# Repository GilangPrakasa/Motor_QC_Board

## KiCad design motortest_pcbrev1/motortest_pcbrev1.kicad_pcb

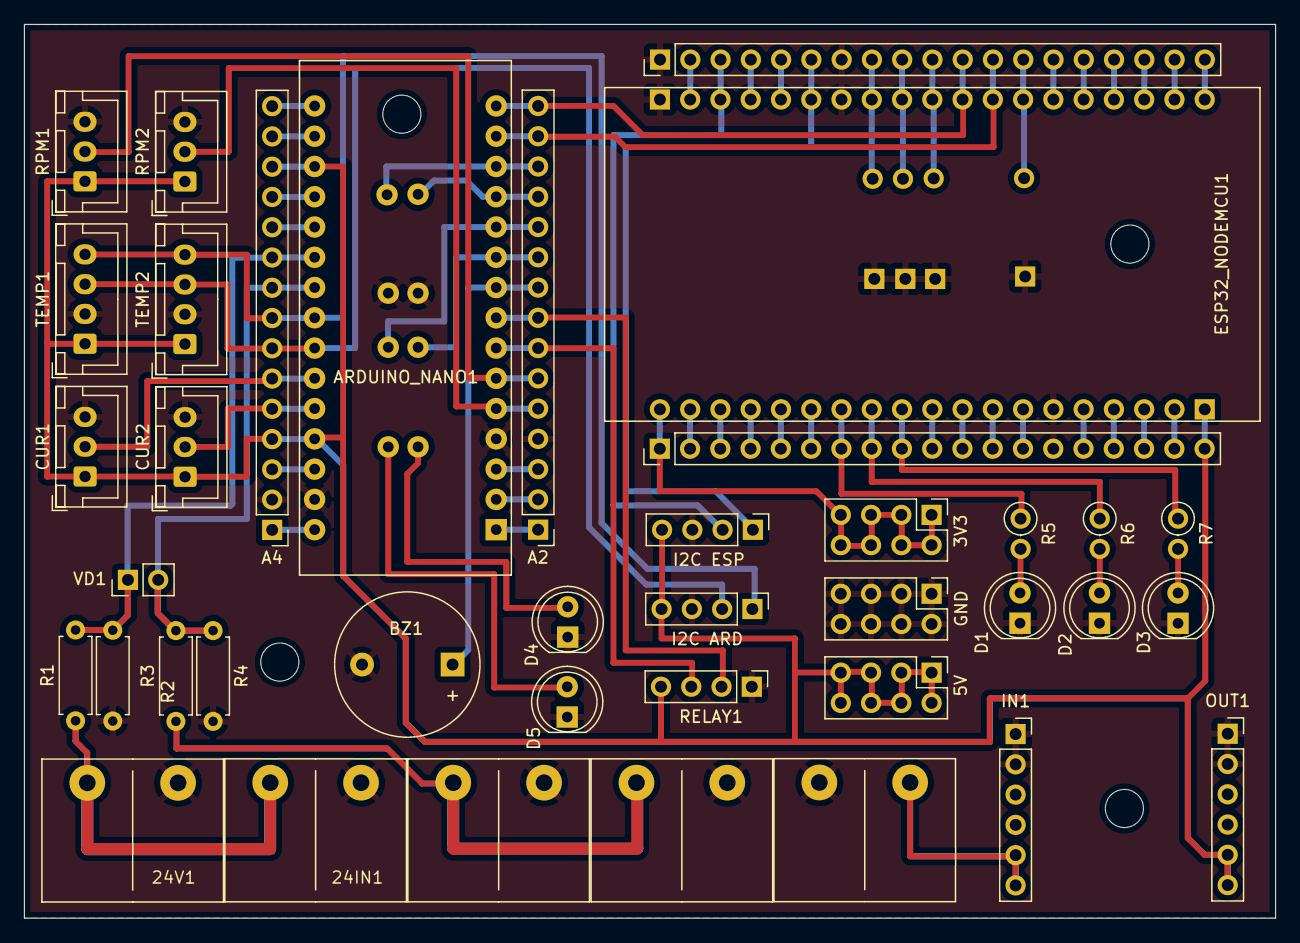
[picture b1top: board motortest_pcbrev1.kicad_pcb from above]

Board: 2 copper layers, 105.0 x 75.0 mm, 43 parts (0 on the bottom side), 67 nets.

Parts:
3V3, 5V: PinHeader_2x04_P2.54mm_Vertical
12IN1, 12V1, 24IN1, 24V1: KF7.62_2P
 : MountingHole_3.2mm_M3_ISO14580
 #2,  #5: PinHeader_1x19_P2.54mm_Vertical
 #3,  #4,  #6: MountingHole_3.2mm_M3_ISO14580
A2, A4: PinHeader_1x15_P2.54mm_Vertical
ARDUINO_NANO1: SHIELD_ARDUINO_NANO
BOARD1: KF7.62_2P
BZ1: Buzzer; Buzzer_12x9.5RM7.6
CUR1, CUR2: JST_XH_B3B-XH-A_1x03_P2.50mm_Vertical
D1, D2, D3, D4, D5: LED_D5.0mm
ESP32_NODEMCU1: MODULE_ESP32_NODEMCU
GND: PinHeader_2x04_P2.54mm_Vertical
I2C ARD, I2C ESP: PinHeader_1x04_P2.54mm_Vertical
IN1: PinSocket_1x06_P2.54mm_Vertical
OUT1: PinSocket_1x06_P2.54mm_Vertical
R1: 10k; R_Axial_DIN0207_L6.3mm_D2.5mm_P7.62mm_Horizontal
R2: 2.2k; R_Axial_DIN0207_L6.3mm_D2.5mm_P7.62mm_Horizontal
R3: 4.7k; R_Axial_DIN0207_L6.3mm_D2.5mm_P7.62mm_Horizontal
R4: 3.3k; R_Axial_DIN0207_L6.3mm_D2.5mm_P7.62mm_Horizontal
R5, R6, R7: R; R_Axial_DIN0207_L6.3mm_D2.5mm_P2.54mm_Vertical
RELAY1: PinHeader_1x04_P2.54mm_Vertical
RPM1, RPM2: JST_XH_B3B-XH-A_1x03_P2.50mm_Vertical
TEMP1, TEMP2: JST_XH_B4B-XH-A_1x04_P2.50mm_Vertical
VD1: PinHeader_1x02_P2.54mm_Vertical

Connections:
/3V3A: A4.14, ARDUINO_NANO1.17 (3V3)
/3V3E: 3V3.1, 3V3.2, 3V3.3, 3V3.4, 3V3.5, 3V3.6, 3V3.7, 3V3.8, #2.1, ESP32_NODEMCU1.J5_19 (3V3)
/5VE: 5V.1, 5V.2, 5V.3, 5V.4, 5V.5, 5V.6, 5V.7, 5V.8, #2.19, A4.4, A4.13, ARDUINO_NANO1.18 (AREF), ARDUINO_NANO1.27 (+5V), CUR1.1, CUR2.1, ESP32_NODEMCU1.J5_1 (5V), I2C ARD.4, I2C ESP.4, OUT1.5, OUT1.6, RELAY1.4, RPM1.1, RPM2.1, TEMP1.1, TEMP2.1
/24IN: BOARD1.1, IN1.5, IN1.6
/+12: 12IN1.2, 12V1.2, R3.1
/+24: 24IN1.2, 24V1.2, R1.1
/A0: A4.12, ARDUINO_NANO1.19 (A0)
/A1: A4.11, ARDUINO_NANO1.20 (A1)
/A2: A4.10, ARDUINO_NANO1.21 (A2), R1.2, R2.1, VD1.1
/A3: A4.9, ARDUINO_NANO1.22 (A3), R3.2, R4.1, VD1.2
/A4: A4.8, ARDUINO_NANO1.23 (A4), I2C ARD.1, TEMP1.4, TEMP2.4
/A5: A4.7, ARDUINO_NANO1.24 (A5), I2C ARD.2, TEMP1.3, TEMP2.3
/A6: A4.6, ARDUINO_NANO1.25 (A6), CUR1.2
/A7: A4.5, ARDUINO_NANO1.26 (A7), CUR2.2
/CLK: #5.19, ESP32_NODEMCU1.J4_19 (CLK)
/CMD: #2.18, ESP32_NODEMCU1.J5_2 (CMD)
/D0: A2.2, ARDUINO_NANO1.2 (D0/RX)
/D1: A2.1, ARDUINO_NANO1.1 (D1/TX)
/D2: A2.5, ARDUINO_NANO1.5 (D2), RPM2.2
/D3: A2.6, ARDUINO_NANO1.6 (D3), RPM1.2
/D4: A2.7, ARDUINO_NANO1.7 (D4), RELAY1.3
/D5: A2.8, ARDUINO_NANO1.8 (D5), RELAY1.2
/D6: A2.9, ARDUINO_NANO1.9 (D6), BZ1.1 (-)
/D7: A2.10, ARDUINO_NANO1.10 (D7)
/D8: A2.11, ARDUINO_NANO1.11 (D8)
/D9: A2.12, ARDUINO_NANO1.12 (D9)
/D10: A2.13, ARDUINO_NANO1.13 (D10)
/D11: #5.12, A2.14, ARDUINO_NANO1.14 (D11/MOSI), ESP32_NODEMCU1.J4_12 (G16)
/D12: #5.11, A2.15, ARDUINO_NANO1.15 (D12/MISO), ESP32_NODEMCU1.J4_11 (G17)
/D13: A4.15, ARDUINO_NANO1.16 (D13/SCK)
/EN: #2.2, ESP32_NODEMCU1.J5_18 (EN)
/G0: #5.14, ESP32_NODEMCU1.J4_14 (G0)
/G2: #5.15, ESP32_NODEMCU1.J4_15 (G2)
/G4: #5.13, ESP32_NODEMCU1.J4_13 (G4)
/G5: #5.10, ESP32_NODEMCU1.J4_10 (G5)
/G12: #2.13, ESP32_NODEMCU1.J5_7 (G12)
/G13: #2.15, ESP32_NODEMCU1.J5_5 (G13)
/G14: #2.12, ESP32_NODEMCU1.J5_8 (G14)
/G15: #5.16, ESP32_NODEMCU1.J4_16 (G15)
/G18: #5.9, ESP32_NODEMCU1.J4_9 (G18)
/G19: #5.8, ESP32_NODEMCU1.J4_8 (G19)
/G21: #5.6, ESP32_NODEMCU1.J4_6 (G21), I2C ESP.1
/G22: #5.3, ESP32_NODEMCU1.J4_3 (G22), I2C ESP.2
/G23: #5.2, ESP32_NODEMCU1.J4_2 (G23)
/G25: #2.9, ESP32_NODEMCU1.J5_11 (G25), R7.1
/G26: #2.10, ESP32_NODEMCU1.J5_10 (G26)
/G27: #2.11, ESP32_NODEMCU1.J5_9 (G27)
/G32: #2.7, ESP32_NODEMCU1.J5_13 (G32), R5.1
/G33: #2.8, ESP32_NODEMCU1.J5_12 (G33), R6.1
/G34: #2.5, ESP32_NODEMCU1.J5_15 (G34)
/G35: #2.6, ESP32_NODEMCU1.J5_14 (G35)
/GND: 12IN1.1, 12V1.1, 24IN1.1, 24V1.1, #2.14, #5.1, #5.7, A2.4, A4.2, ARDUINO_NANO1.4 (COM/GND), ARDUINO_NANO1.29 (COM/GND), BOARD1.2, BZ1.2 (+), CUR1.3, CUR2.3, D1.1 (K), D2.1 (K), D3.1 (K), D4.1 (K), D5.1 (K), ESP32_NODEMCU1.J4_1 (GND), ESP32_NODEMCU1.J4_7 (GND), ESP32_NODEMCU1.J5_6 (GND), GND.1, GND.2, GND.3, GND.4, GND.5, GND.6, GND.7, GND.8, I2C ARD.3, I2C ESP.3, IN1.1, IN1.2, OUT1.1, OUT1.2, R2.2, R4.2, RELAY1.1, RPM1.3, RPM2.3, TEMP1.2, TEMP2.2
/RESET: A2.3, A4.3, ARDUINO_NANO1.3 (RESET), ARDUINO_NANO1.28 (RESET)
/RXD: #5.5, ESP32_NODEMCU1.J4_5 (RXD)
/SD0: #5.18, ESP32_NODEMCU1.J4_18 (SD0)
/SD1: #5.17, ESP32_NODEMCU1.J4_17 (SD1)
/SD2: #2.16, ESP32_NODEMCU1.J5_4 (SD2)
/SD3: #2.17, ESP32_NODEMCU1.J5_3 (SD3)
/SN: #2.4, ESP32_NODEMCU1.J5_16 (SN)
/SP: #2.3, ESP32_NODEMCU1.J5_17 (SP)
/TXD: #5.4, ESP32_NODEMCU1.J4_4 (TXD)
/VIN: A4.1, ARDUINO_NANO1.30 (VIN)
/X: ARDUINO_NANO1.29 (COM/GND), D4.2 (A)
/Y: ARDUINO_NANO1.29 (COM/GND), D5.2 (A)
unnamed: D1.2 (A), R5.2
unnamed: D2.2 (A), R6.2
unnamed: D3.2 (A), R7.2

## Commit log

2024-04-04 V1.0.0
